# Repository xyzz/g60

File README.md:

# g60

A simple 3d-printable oring gasket keyboard.

## Known issues

Depending on 3d print tolerances, plate and PCB edges might scratch against the corners of the case. Ideally, the outlines of both should be reduced a little bit. Unfortunately, these changes will not be done as a result of me losing interest in the project due to availability of [Bakeneko](https://github.com/kkatano/bakeneko-60-aluminum-case).

## Compatibility

The PCB is not compatible with other cases due to custom mounting point cutouts and USB position. In turn, the case is also not compatible with any third-party PCBs.

## Oring size

Around 180mm ID and 3.5mm CS, for example  AS568-263 should work fine.

## Machinability

The case should be machinable, however it was not tested and I cannot suggest getting it machined due to extremely simplistic design (ie just make a Bakeneko instead).

## License

This project is licensed under [CC0](https://creativecommons.org/share-your-work/public-domain/cc0/), see the LICENSE file for more details, or [tldrlegal.com](https://tldrlegal.com/license/creative-commons-cc0-1.0-universal) for a summary.

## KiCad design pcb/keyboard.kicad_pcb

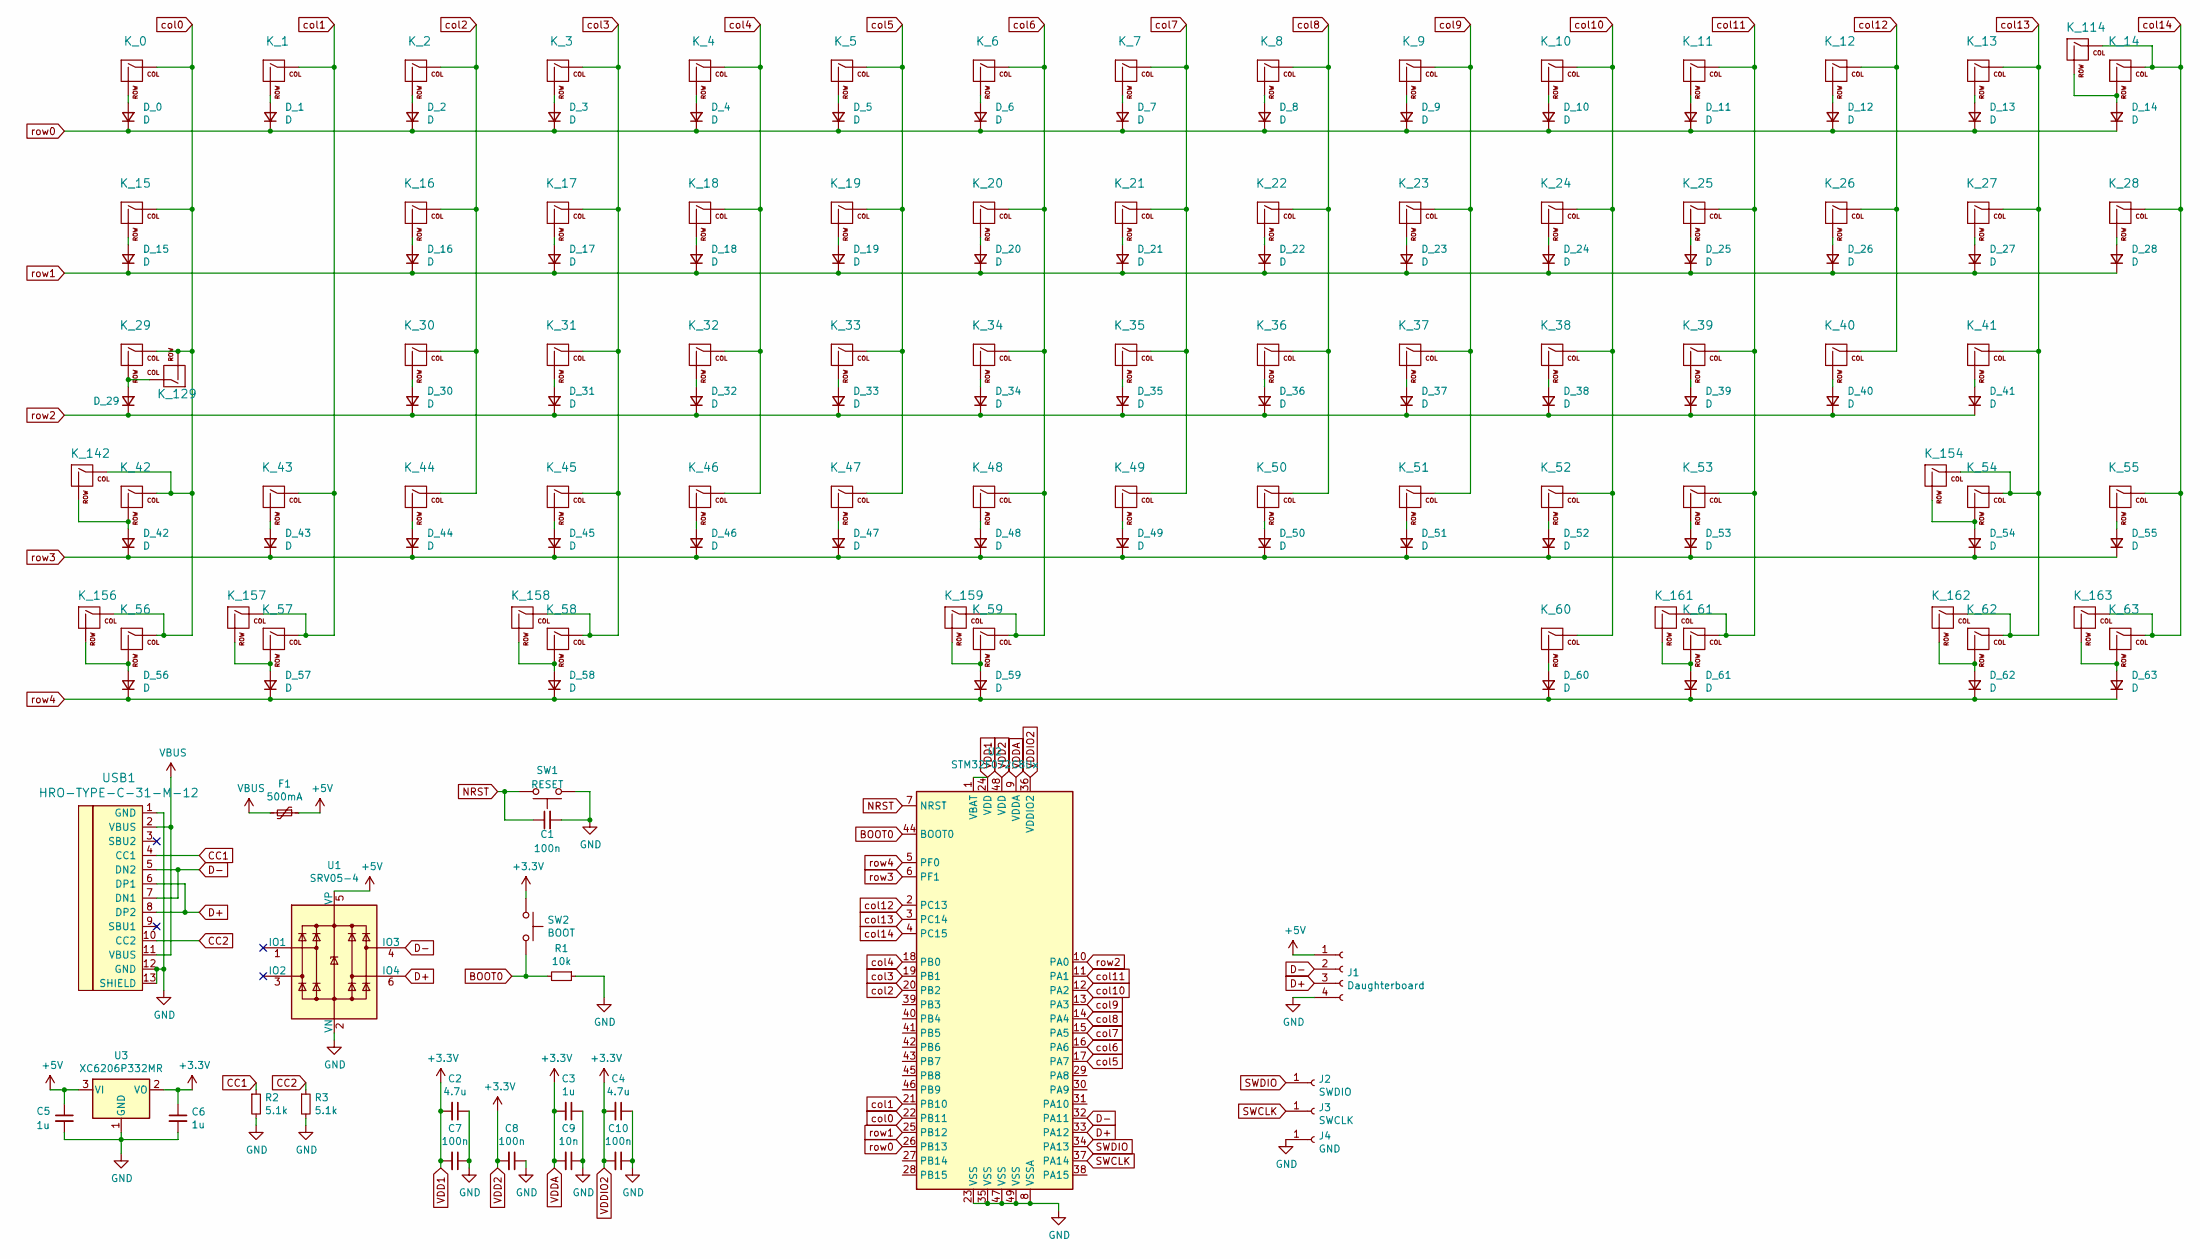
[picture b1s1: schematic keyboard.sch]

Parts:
C1, C7, C8, C10: 100n; C_0603_1608Metric; LCSC C14663
C2, C4: 4.7u; C_0603_1608Metric; LCSC C19666
C3, C5, C6: 1u; C_0603_1608Metric; LCSC C15849
C9: 10n; C_0603_1608Metric; LCSC C57112
D_0, D_1, D_2, D_3, D_4, D_5, D_6, D_7, D_8, D_9, D_10, D_11, D_12, D_13, D_14, D_15, D_16, D_17, D_18, D_19, D_20, D_21, D_22, D_23, D_24, D_25, D_26, D_27, D_28, D_29, D_30, D_31, D_32, D_33, D_34, D_35, D_36, D_37, D_38, D_39, D_40, D_41, D_42, D_43, D_44, D_45, D_46, D_47, D_48, D_49, D_50, D_51, D_52, D_53, D_54, D_55, D_56, D_57, D_58, D_59, D_60, D_61, D_62, D_63: D; D_SOD-123; LCSC C81598
F1: 500mA; Fuse_1206_3216Metric; LCSC C369159
J1: Daughterboard; JST_SH_SM04B-SRSS-TB_1x04-1MP_P1.00mm_Horizontal
J2: SWDIO; TestPoint_Pad_D1.5mm
J3: SWCLK; TestPoint_Pad_D1.5mm
J4: GND; TestPoint_Pad_D1.5mm
K_0, K_1, K_2, K_3, K_4, K_5, K_6, K_7, K_8, K_9, K_10, K_11, K_12, K_13, K_14, K_16, K_17, K_18, K_19, K_20, K_21, K_22, K_23, K_24, K_25, K_26, K_27, K_30, K_31, K_32, K_33, K_34, K_35, K_36, K_37, K_38, K_39, K_40, K_43, K_44, K_45, K_46, K_47, K_48, K_49, K_50, K_51, K_52, K_53, K_55: KEYSW; MXOnly-1U-NoLED
K_15, K_28: KEYSW; MXOnly-1.5U-NoLED
K_29: Regular; MXOnly-1.75U-NoLED
K_41: KEYSW; MXOnly-2.25U-NoLED
K_42: KEYSW; MXOnly-1.25U-NoLED
K_54: KEYSW; MXOnly-1.75U-NoLED
K_56, K_57, K_58, K_60, K_61, K_62, K_63: 1.25u; MXOnly-1.25U-NoLED
K_59: 6.25u; MXOnly-6.25U-ReversedStabilizers-NoLED
K_114: MX-NoLED; MXOnly-2U-NoLED
K_129: Stepped; MXOnly-1.25U-NoLED
K_142: MX-NoLED; MXOnly-2.25U-NoLED
K_154: MX-NoLED; MXOnly-2.75U-NoLED
K_156, K_158, K_161, K_163: 1.5u; MXOnly-1.5U-NoLED
K_157, K_162: 1u; MXOnly-1U-NoLED
K_159: 7u; MXOnly-7U-ReversedStabilizers-NoLED
R1: 10k; R_0603_1608Metric; LCSC C25804
R2, R3: 5.1k; R_0603_1608Metric; LCSC C23186
SW1: RESET; SW_SPST_TL3342; LCSC C318884
SW2: BOOT; SW_SPST_TL3342; LCSC C318884
U1: SRV05-4; SOT-23-6; LCSC C85364
U2: STM32F072C8Ux; QFN-48-1EP_7x7mm_P0.5mm_EP5.6x5.6mm; LCSC C92504
U3: XC6206P332MR; SOT-23; LCSC C5446
USB1: HRO-TYPE-C-31-M-12

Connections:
+5V: C5.1, F1.1, J1.1, U1.5 (VP), U3.3 (VI)
BOOT0: R1.2, SW2.2, U2.44 (BOOT0)
CC1: R2.1, USB1.4 (CC1)
CC2: R3.1, USB1.10 (CC2)
D+: J1.3, U1.6 (IO4), U2.33 (PA12), USB1.6 (DP1), USB1.8 (DP2)
D-: J1.2, U1.4 (IO3), U2.32 (PA11), USB1.5 (DN2), USB1.7 (DN1)
GND: C1.2, C2.1, C3.1, C4.1, C5.2, C6.2, C7.1, C8.1, C9.1, C10.1, J1.4, J4.1, R1.1, R2.2, R3.2, SW1.1, U1.2 (VN), U2.8 (VSSA), U2.23 (VSS), U2.35 (VSS), U2.47 (VSS), U2.49 (VSS), U3.1 (GND), USB1.1 (GND), USB1.12 (GND), USB1.13 (SHIELD)
NRST: C1.1, SW1.2, U2.7 (NRST)
unnamed: D_0.2 (A), K_0.2 (ROW)
unnamed: D_1.2 (A), K_1.2 (ROW)
unnamed: D_2.2 (A), K_2.2 (ROW)
unnamed: D_3.2 (A), K_3.2 (ROW)
unnamed: D_4.2 (A), K_4.2 (ROW)
unnamed: D_5.2 (A), K_5.2 (ROW)
unnamed: D_6.2 (A), K_6.2 (ROW)
unnamed: D_7.2 (A), K_7.2 (ROW)
unnamed: D_8.2 (A), K_8.2 (ROW)
unnamed: D_9.2 (A), K_9.2 (ROW)
unnamed: D_10.2 (A), K_10.2 (ROW)
unnamed: D_11.2 (A), K_11.2 (ROW)
unnamed: D_12.2 (A), K_12.2 (ROW)
unnamed: D_13.2 (A), K_13.2 (ROW)
unnamed: D_14.2 (A), K_14.2 (ROW), K_114.2 (ROW)
unnamed: D_15.2 (A), K_15.2 (ROW)
unnamed: D_16.2 (A), K_16.2 (ROW)
unnamed: D_17.2 (A), K_17.2 (ROW)
unnamed: D_18.2 (A), K_18.2 (ROW)
unnamed: D_19.2 (A), K_19.2 (ROW)
unnamed: D_20.2 (A), K_20.2 (ROW)
unnamed: D_21.2 (A), K_21.2 (ROW)
unnamed: D_22.2 (A), K_22.2 (ROW)
unnamed: D_23.2 (A), K_23.2 (ROW)
unnamed: D_24.2 (A), K_24.2 (ROW)
unnamed: D_25.2 (A), K_25.2 (ROW)
unnamed: D_26.2 (A), K_26.2 (ROW)
unnamed: D_27.2 (A), K_27.2 (ROW)
unnamed: D_28.2 (A), K_28.2 (ROW)
unnamed: D_29.2 (A), K_29.2 (ROW), K_129.1 (COL)
unnamed: D_30.2 (A), K_30.2 (ROW)
unnamed: D_31.2 (A), K_31.2 (ROW)
unnamed: D_32.2 (A), K_32.2 (ROW)
unnamed: D_33.2 (A), K_33.2 (ROW)
unnamed: D_34.2 (A), K_34.2 (ROW)
unnamed: D_35.2 (A), K_35.2 (ROW)
unnamed: D_36.2 (A), K_36.2 (ROW)
unnamed: D_37.2 (A), K_37.2 (ROW)
unnamed: D_38.2 (A), K_38.2 (ROW)
unnamed: D_39.2 (A), K_39.2 (ROW)
unnamed: D_40.2 (A), K_40.2 (ROW)
unnamed: D_41.2 (A), K_41.2 (ROW)
unnamed: D_42.2 (A), K_42.2 (ROW), K_142.2 (ROW)
unnamed: D_43.2 (A), K_43.2 (ROW)
unnamed: D_44.2 (A), K_44.2 (ROW)
unnamed: D_45.2 (A), K_45.2 (ROW)
unnamed: D_46.2 (A), K_46.2 (ROW)
unnamed: D_47.2 (A), K_47.2 (ROW)
unnamed: D_48.2 (A), K_48.2 (ROW)
unnamed: D_49.2 (A), K_49.2 (ROW)
unnamed: D_50.2 (A), K_50.2 (ROW)
unnamed: D_51.2 (A), K_51.2 (ROW)
unnamed: D_52.2 (A), K_52.2 (ROW)
unnamed: D_53.2 (A), K_53.2 (ROW)
unnamed: D_54.2 (A), K_54.2 (ROW), K_154.2 (ROW)
unnamed: D_55.2 (A), K_55.2 (ROW)
unnamed: D_56.2 (A), K_56.2 (ROW), K_156.2 (ROW)
unnamed: D_57.2 (A), K_57.2 (ROW), K_157.2 (ROW)
unnamed: D_58.2 (A), K_58.2 (ROW), K_158.2 (ROW)
unnamed: D_59.2 (A), K_59.2 (ROW), K_159.2 (ROW)
unnamed: D_60.2 (A), K_60.2 (ROW)
unnamed: D_61.2 (A), K_61.2 (ROW), K_161.2 (ROW)
unnamed: D_62.2 (A), K_62.2 (ROW), K_162.2 (ROW)
unnamed: D_63.2 (A), K_63.2 (ROW), K_163.2 (ROW)
SWCLK: J3.1, U2.37 (PA14)
SWDIO: J2.1, U2.34 (PA13)
VBUS: F1.2, USB1.2 (VBUS), USB1.11 (VBUS)
VDD1: C2.2, C3.2, C4.2, C6.1, C7.2, C8.2, C9.2, C10.2, SW2.1, U2.1 (VBAT), U2.9 (VDDA), U2.24 (VDD), U2.36 (VDDIO2), U2.48 (VDD), U3.2 (VO)
col0: K_0.1 (COL), K_15.1 (COL), K_29.1 (COL), K_42.1 (COL), K_56.1 (COL), K_129.2 (ROW), K_142.1 (COL), K_156.1 (COL), U2.22 (PB11)
col1: K_1.1 (COL), K_43.1 (COL), K_57.1 (COL), K_157.1 (COL), U2.21 (PB10)
col2: K_2.1 (COL), K_16.1 (COL), K_30.1 (COL), K_44.1 (COL), U2.20 (PB2)
col3: K_3.1 (COL), K_17.1 (COL), K_31.1 (COL), K_45.1 (COL), K_58.1 (COL), K_158.1 (COL), U2.19 (PB1)
col4: K_4.1 (COL), K_18.1 (COL), K_32.1 (COL), K_46.1 (COL), U2.18 (PB0)
col5: K_5.1 (COL), K_19.1 (COL), K_33.1 (COL), K_47.1 (COL), U2.17 (PA7)
col6: K_6.1 (COL), K_20.1 (COL), K_34.1 (COL), K_48.1 (COL), K_59.1 (COL), K_159.1 (COL), U2.16 (PA6)
col7: K_7.1 (COL), K_21.1 (COL), K_35.1 (COL), K_49.1 (COL), U2.15 (PA5)
col8: K_8.1 (COL), K_22.1 (COL), K_36.1 (COL), K_50.1 (COL), U2.14 (PA4)
col9: K_9.1 (COL), K_23.1 (COL), K_37.1 (COL), K_51.1 (COL), U2.13 (PA3)
col10: K_10.1 (COL), K_24.1 (COL), K_38.1 (COL), K_52.1 (COL), K_60.1 (COL), U2.12 (PA2)
col11: K_11.1 (COL), K_25.1 (COL), K_39.1 (COL), K_53.1 (COL), K_61.1 (COL), K_161.1 (COL), U2.11 (PA1)
col12: K_12.1 (COL), K_26.1 (COL), K_40.1 (COL), U2.2 (PC13)
col13: K_13.1 (COL), K_27.1 (COL), K_41.1 (COL), K_54.1 (COL), K_62.1 (COL), K_154.1 (COL), K_162.1 (COL), U2.3 (PC14)
col14: K_14.1 (COL), K_28.1 (COL), K_55.1 (COL), K_63.1 (COL), K_114.1 (COL), K_163.1 (COL), U2.4 (PC15)
row0: D_0.1 (K), D_1.1 (K), D_2.1 (K), D_3.1 (K), D_4.1 (K), D_5.1 (K), D_6.1 (K), D_7.1 (K), D_8.1 (K), D_9.1 (K), D_10.1 (K), D_11.1 (K), D_12.1 (K), D_13.1 (K), D_14.1 (K), U2.26 (PB13)
row1: D_15.1 (K), D_16.1 (K), D_17.1 (K), D_18.1 (K), D_19.1 (K), D_20.1 (K), D_21.1 (K), D_22.1 (K), D_23.1 (K), D_24.1 (K), D_25.1 (K), D_26.1 (K), D_27.1 (K), D_28.1 (K), U2.25 (PB12)
row2: D_29.1 (K), D_30.1 (K), D_31.1 (K), D_32.1 (K), D_33.1 (K), D_34.1 (K), D_35.1 (K), D_36.1 (K), D_37.1 (K), D_38.1 (K), D_39.1 (K), D_40.1 (K), D_41.1 (K), U2.10 (PA0)
row3: D_42.1 (K), D_43.1 (K), D_44.1 (K), D_45.1 (K), D_46.1 (K), D_47.1 (K), D_48.1 (K), D_49.1 (K), D_50.1 (K), D_51.1 (K), D_52.1 (K), D_53.1 (K), D_54.1 (K), D_55.1 (K), U2.6 (PF1)
row4: D_56.1 (K), D_57.1 (K), D_58.1 (K), D_59.1 (K), D_60.1 (K), D_61.1 (K), D_62.1 (K), D_63.1 (K), U2.5 (PF0)

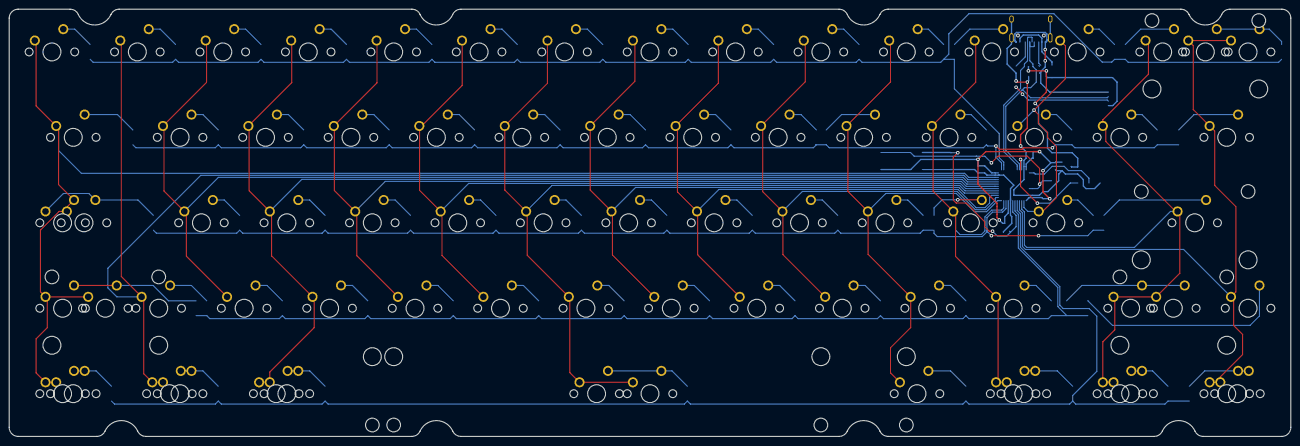
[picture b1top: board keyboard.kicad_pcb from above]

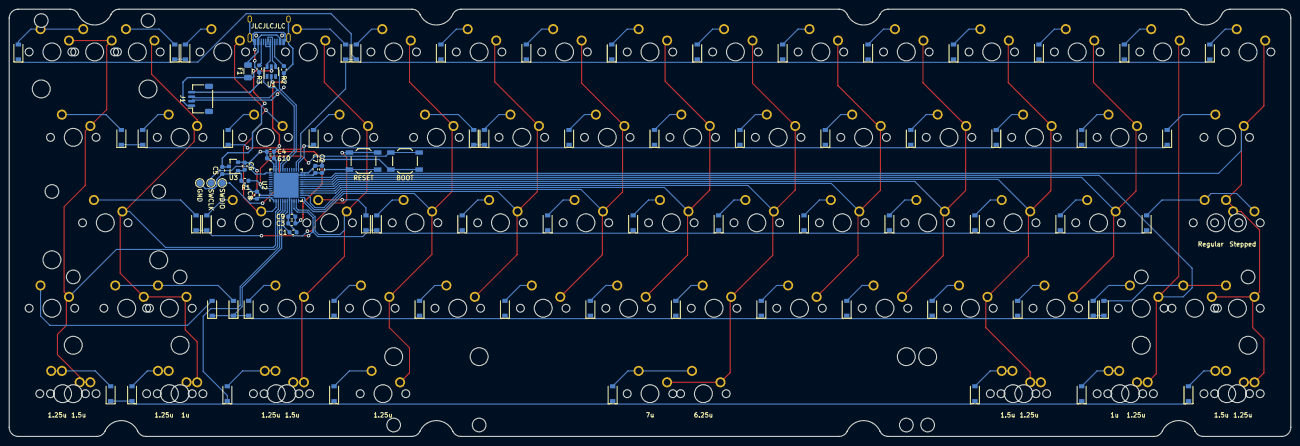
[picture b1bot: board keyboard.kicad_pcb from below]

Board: 2 copper layers, 285.8 x 95.3 mm, 163 parts (88 on the bottom side), 96 nets.
